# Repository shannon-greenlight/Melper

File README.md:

# The Melper
The Melper converts a Moog case into a powered Eurorack case.

It requires +12V as an input and generates -12V and +5V.
These 3 voltage rails supply 6 Eurorack power connectors.
Three LEDs monitor the supply rails.
It is targeted to Moog cases, but can be used in any case that has +12V.
The 12 volt wall wart that Moog supplies works well. 

This repo contains the schematic and layout files needed to create the Melper.
These files are for KiCAD Version: 8.0.8

The repo contains the BOM files that are used to buy the components.
These are found in the _BOM_ folder.
The BOM files for DigiKey and JLCPCB are provided in .csv format.
Other suppliers typically will accept these files with minor modifications.

The repo also contains the files needed for fabrication. These are found in the _fab_ folder.
These include the gerber files, which are provided both as a zip file and as the full unzipped folder structure.
Also included in the _fab_ folder are the files needed for pick-and-place.
The .xlsx file is the pick-and-place file. It is formatted for JLCPCB.
The raw position files are found in the _pos_ folder.

# Specs
The Melper derives -12V and +5V from the +12V supply.
- -12V
	- Voltage range: -11.75V thru -12.25V
	- Maximum current: 200mA
	- Line regulation: 15mV
	- Load regulation: 20mV
	- Ripple: 230mV
- +5V (see - [LM7805](https://www.ti.com/lit/ds/symlink/lm7800.pdf))
	- Voltage range: +4.8V thru +5.2V
	- Maximum current: 500mA @ 25C (more if heat-sink is used)
	- Line regulation: 3mV typ.
	- Load regulation: 10mV typ.
	- Ripple rejection: 80dB typ.

# Making Changes
The process of making changes usually starts with altering the schematic followed by other actions as required.
This requires a properly configured KiCAD installation. Download the KiCAD [repo](https://github.com/shannon-greenlight/KiCAD) and follow the instructions in the README to install.
When the system is configured follow the steps outlined below. Some steps are optional depending on what has changed.

These procedures have been optimized for use with Digi-Key and JLCPCB. They should be a good starting point for use with other vendors.

- Update schematic
- If any parts have changed, Update BOMs
	- From KiCAD Schematic Editor, run Tools->Generate Legacy Bill of Materials using bom2grouped_csv.xsl
		- bom2grouped_csv.xsl is found in the Greenface KiCAD repo.
		- Here is a sample command line: xsltproc -o "%O.csv" "C:\Users\shann\Dropbox\KiCAD\bom2grouped_csv.xsl" "%I"
		- This creates a .csv and an xsl file. The xml file is used in the next step.
	- Run _generate_boms.bat_
		- This creates 3 .csv files
			- BOM\Digi-Key\Melper_full.csv (all components)
			- BOM\Digi-Key\Melper_split.csv (just components not found in LCSC BOM)
			- BOM\LCSC\Melper_bom.csv (just components to be assembled by JLCPCB)
		- generate_boms.bat requires Python and the Greenface Python [libraries](https://github.com/shannon-greenlight/PYTHON_BOM) to be installed
			- Place the Greenface Python folder in a convienient place on your computer and set the variable %plugin_dir% to point to that folder location.
			- Python is invoked as 'py' in the batch file. This may need to be changed depending on your Python installation.
- Update layout if required
	- Plot the Gerber files
		- Set the output directory to _fab\gerber\\_
		- Make sure to Generate Drill Files
		- Create a zip archive of the Gerber files. (This is required by JLCPCB)
			- Use Windows Send To Compressed Folder. Rename the resulting file to melper_gerbers.zip
			- Alternatively, use zip_gerbers.bat
			- zip_gerbers.bat requires 7z.exe
			- Edit this file if 7z.exe is installed somewhere other than C:\Program Files\7-Zip
	- Create the pick-and-place files
		- From KiCAD PCB Editor, run File->Fabrication Outputs->Component Placement
		- Set the output directory to _fab\pos\\_
		- This creates the files used by the next step
		- Update melper_cpl.xlsx
			- melper_cpl.xlsx uses Excel Queries to convert pos\Melper-top-pos.csv into a format compatible with JLCPCB
			- Excel requires an absolute path to the source folder of the data. Edit the query to enter the path to your project.
			- *note: This process does not produce a perfect placement file due to differences in how KiCAD and JLCPCB orient components. However, JLCPCB is able to use the file without problems. So, even if the placement looks wrong when specifying the build, they will use the file and produce correct boards.
			- **note: There is probably a KiCAD plugin available that does a better job. The user is encouraged to try this route and report the results back.
- Upload to JLCPCB
	- JLCPCB requires the following files:
		- fab\melper_gerbers.zip
		- fab\melper_cpl.xlsx (only needed for assembly)
		- bom\LCSC\Melper_bom.csv (only needed for assembly)

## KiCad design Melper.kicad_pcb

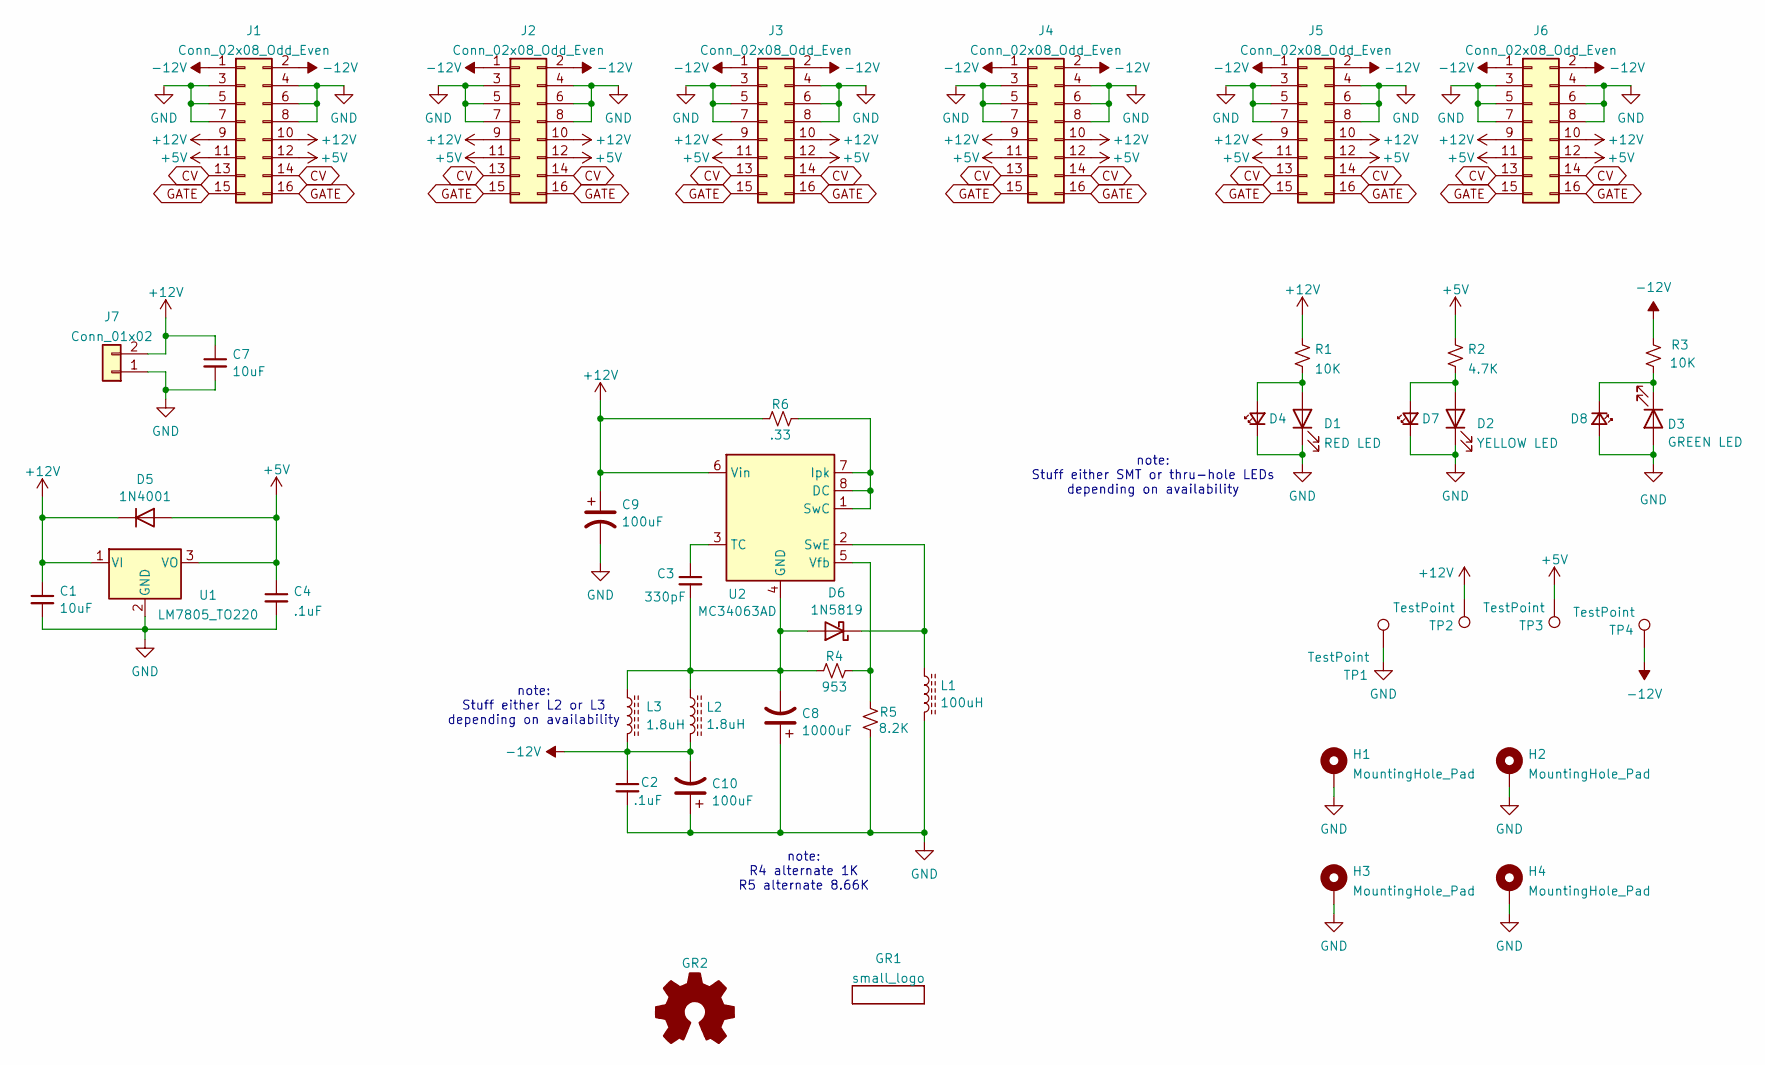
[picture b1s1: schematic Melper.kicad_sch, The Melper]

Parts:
C1, C7: 10uF; C_Disc_D5.1mm_W3.2mm_P5.00mm; Digi-Key Part 445-173437-1-ND
C2, C4: .1uF; C_Disc_D4.3mm_W1.9mm_P5.00mm; Digi-Key Part 399-9877-1-ND
C3: 330pF; C_Disc_D4.3mm_W1.9mm_P5.00mm; Digi-Key Part 399-4231-ND
C8: 1000uF; CP_Radial_D10.0mm_P5.00mm; Digi-Key Part 1189-1545-1-ND
C9, C10: 100uF; CP_Radial_D6.3mm_P2.50mm; Digi-Key Part 1189-1300-ND
D1: RED LED; LED_D3.0mm; Digi-Key Part 160-1035-ND
D2: YELLOW LED; LED_D3.0mm; Digi-Key Part 160-1961-ND
D3: GREEN LED; LED_D3.0mm; Digi-Key Part 732-5008-ND
D4: Red SMT LED; LED_0603_1608Metric_Pad1.05x0.95mm_HandSolder; LCSC Part # C2286
D5: 1N4001; D_DO-41_SOD81_P10.16mm_Horizontal; Digi-Key Part 1N4001RLGOSCT-ND
D6: 1N5819; D_DO-41_SOD81_P7.62mm_Horizontal; Digi-Key Part 497-6610-1-ND
D7: Yellow SMT LED; LED_0603_1608Metric_Pad1.05x0.95mm_HandSolder; LCSC Part # C72038
D8: Blue SMT LED; LED_0603_1608Metric_Pad1.05x0.95mm_HandSolder; LCSC Part # C2288
GR1: small_logo; small_face
GR2: Logo_Open_Hardware_Small; OSHW-Logo_5.7x6mm_SilkScreen
H1, H2, H3, H4: MountingHole_Pad; MountingHole_3.2mm_M3_DIN965_Pad
J1, J2, J3, J4, J5, J6: Conn_02x08_Odd_Even; PinHeader_2x08_P2.54mm_Vertical; Digi-Key Part S9171-ND
J7: Conn_01x02; PinHeader_1x02_P2.54mm_Vertical; Digi-Key Part 900-0022232021-ND
L1: 100uH; L_Radial_D8.7mm_P5.00mm_Fastron_07HCP; Digi-Key Part RLB0914-101KL-ND
L2: 1.8uH; L_Axial_L9.5mm_D4.0mm_P12.70mm_Horizontal_Fastron_SMCC; Digi-Key Part 495-76032-1-ND
L3: 1.8uH; L_Sunlord_SWPA4012S; LCSC Part # C96867
R1, R3: 10K; R_Axial_DIN0207_L6.3mm_D2.5mm_P10.16mm_Horizontal; Digi-Key Part S10KQCT-ND
R2: 4.7K; R_Axial_DIN0207_L6.3mm_D2.5mm_P10.16mm_Horizontal; Digi-Key Part CF14JT4K70CT-ND
R4: 953; R_Axial_DIN0207_L6.3mm_D2.5mm_P10.16mm_Horizontal; Digi-Key Part 13-MFR-25FRF52-953RCT-ND
R5: 8.2K; R_Axial_DIN0207_L6.3mm_D2.5mm_P10.16mm_Horizontal; Digi-Key Part MFR-25FBF52-8K2-ND
R6: .33; R_Axial_DIN0207_L6.3mm_D2.5mm_P10.16mm_Horizontal; Digi-Key Part A138238CT-ND
TP1: TestPoint; TestPoint_Keystone_5005-5009_Compact; Digi-Key Part 36-5006-ND
TP2, TP3, TP4: TestPoint; TestPoint_Pad_D2.0mm
U1: LM7805_TO220; TO-220-3_Horizontal_TabDown; Digi-Key Part 497-12404-ND
U2: MC34063AD; DIP-8_W7.62mm_LongPads; Digi-Key Part 497-7412-5-ND

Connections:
+5V: C4.1, D5.2 (A), J1.11, J1.12, J2.11, J2.12, J3.11, J3.12, J4.11, J4.12, J5.11, J5.12, J6.11, J6.12, R2.1, TP3.1, U1.3 (VO)
+12V: C1.1, C7.1, C9.1, D5.1 (K), J1.9, J1.10, J2.9, J2.10, J3.9, J3.10, J4.9, J4.10, J5.9, J5.10, J6.9, J6.10, J7.2, R1.1, R6.1, TP2.1, U1.1 (VI), U2.6 (Vin)
-12V: C2.1, C10.2, J1.1, J1.2, J2.1, J2.2, J3.1, J3.2, J4.1, J4.2, J5.1, J5.2, J6.1, J6.2, L2.2, L3.2, R3.2, TP4.1
CV: J1.13, J1.14, J2.13, J2.14, J3.13, J3.14, J4.13, J4.14, J5.13, J5.14, J6.13, J6.14
GATE: J1.15, J1.16, J2.15, J2.16, J3.15, J3.16, J4.15, J4.16, J5.15, J5.16, J6.15, J6.16
GND: C1.2, C2.2, C4.2, C7.2, C8.1, C9.2, C10.1, D1.1 (K), D2.1 (K), D3.2 (A), D4.1 (K), D7.1 (K), D8.2 (A), H1.1, H2.1, H3.1, H4.1, J1.3, J1.4, J1.5, J1.6, J1.7, J1.8, J2.3, J2.4, J2.5, J2.6, J2.7, J2.8, J3.3, J3.4, J3.5, J3.6, J3.7, J3.8, J4.3, J4.4, J4.5, J4.6, J4.7, J4.8, J5.3, J5.4, J5.5, J5.6, J5.7, J5.8, J6.3, J6.4, J6.5, J6.6, J6.7, J6.8, J7.1, L1.2, R5.1, TP1.1, U1.2 (GND)
unnamed: D1.2 (A), D4.2 (A), R1.2
unnamed: D2.2 (A), D7.2 (A), R2.2
unnamed: D3.1 (K), D8.1 (K), R3.1
unnamed: C3.2, C8.2, D6.2 (A), L2.1, L3.1, R4.1, U2.4 (GND)
unnamed: D6.1 (K), L1.1, U2.2 (SwE)
unnamed: R6.2, U2.1 (SwC), U2.7 (Ipk), U2.8 (DC)
unnamed: C3.1, U2.3 (TC)
unnamed: R4.2, R5.2, U2.5 (Vfb)

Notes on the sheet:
note: Stuff either L2 or L3 depending on availability
note: R4 alternate 1K R5 alternate 8.66K
note: Stuff either SMT or thru-hole LEDs depending on availability

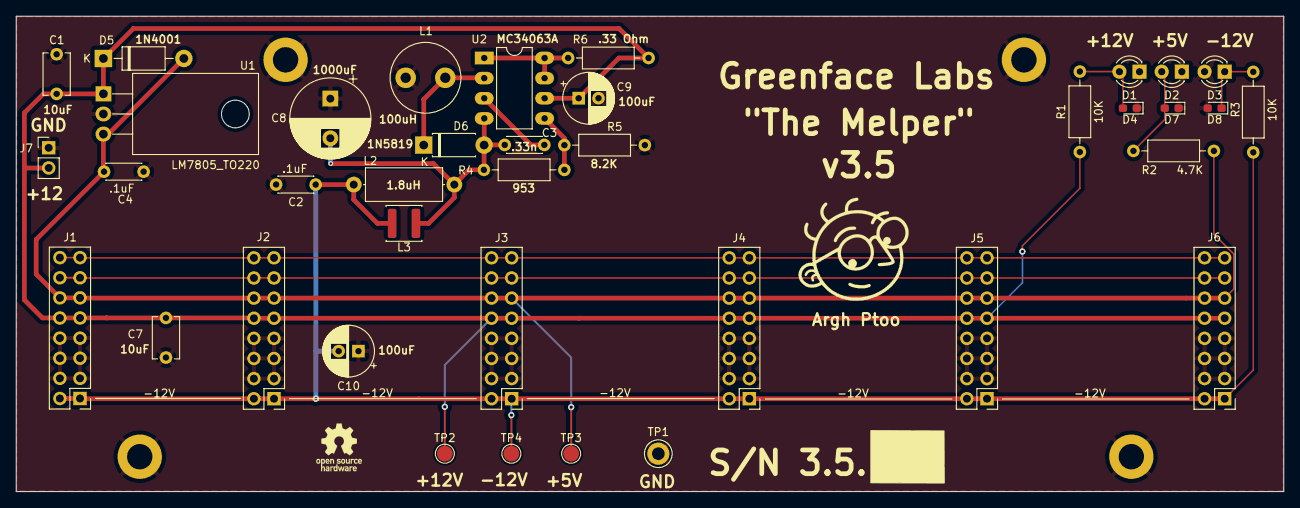
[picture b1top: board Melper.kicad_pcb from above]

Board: 2 copper layers, 160.0 x 60.0 mm, 44 parts (0 on the bottom side), 14 nets.

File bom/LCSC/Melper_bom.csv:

"Designator","Comment","Footprint","JLCPCBPart#"
"C1, C7, ","10uF","Capacitor_THT:C_Disc_D5.1mm_W3.2mm_P5.00mm","C531341 "
"C2, C4, ",".1uF","Capacitor_THT:C_Disc_D4.3mm_W1.9mm_P5.00mm","C84772 "
"C3, ","330pF","Capacitor_THT:C_Disc_D4.3mm_W1.9mm_P5.00mm","C2896045"
"C8, ","1000uF","Capacitor_THT:CP_Radial_D10.0mm_P5.00mm","C43909"
"C9, C10, ","100uF","Capacitor_THT:CP_Radial_D6.3mm_P2.50mm","C45075"
"D4, ","Red SMT LED","LED_SMD:LED_0603_1608Metric_Pad1.05x0.95mm_HandSolder","C2286"
"D5, ","1N4001","Diode_THT:D_DO-41_SOD81_P10.16mm_Horizontal","C895212"
"D6, ","1N5819","Diode_THT:D_DO-41_SOD81_P7.62mm_Horizontal","C110032"
"D7, ","Yellow SMT LED","LED_SMD:LED_0603_1608Metric_Pad1.05x0.95mm_HandSolder","C72038"
"D8, ","Blue SMT LED","LED_SMD:LED_0603_1608Metric_Pad1.05x0.95mm_HandSolder","C2288"
"J1, J2, J3, J4, J5, J6, ","Conn_02x08_Odd_Even","Connector_PinHeader_2.54mm:PinHeader_2x08_P2.54mm_Vertical","C305956"
"J7, ","Conn_01x02","Connector_PinHeader_2.54mm:PinHeader_1x02_P2.54mm_Vertical","C2905434"
"L1, ","100uH","Inductor_THT:L_Radial_D8.7mm_P5.00mm_Fastron_07HCP","C7343084"
"L2, ","1.8uH","Inductor_THT:L_Axial_L9.5mm_D4.0mm_P12.70mm_Horizontal_Fastron_SMCC","C17370623"
"L3, ","1.8uH","Inductor_SMD:L_Sunlord_SWPA4012S","C96867"
"R1, R3, ","10K","Resistor_THT:R_Axial_DIN0207_L6.3mm_D2.5mm_P10.16mm_Horizontal","C57436 "
"R2, ","4.7K","Resistor_THT:R_Axial_DIN0207_L6.3mm_D2.5mm_P10.16mm_Horizontal","C176521"
"R4, ","953","Resistor_THT:R_Axial_DIN0207_L6.3mm_D2.5mm_P10.16mm_Horizontal","C57435"
"R5, ","8.2K","Resistor_THT:R_Axial_DIN0207_L6.3mm_D2.5mm_P10.16mm_Horizontal","C172593"
"R6, ",".33","Resistor_THT:R_Axial_DIN0207_L6.3mm_D2.5mm_P10.16mm_Horizontal","C119970"
"TP1, ","TestPoint","TestPoint:TestPoint_Keystone_5005-5009_Compact","C238124 "
"U1, ","LM7805_TO220","Package_TO_SOT_THT:TO-220-3_Horizontal_TabDown","C111887 "
"U2, ","MC34063AD","Package_DIP:DIP-8_W7.62mm_LongPads","C5180"

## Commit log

2022-12-15 Init checkin of project
2022-12-15 Update Melper.kicad_sch
    Changes LED resistors.
2022-12-15 Adds BOM
2022-12-17 Work on images.
2023-10-19 Version 2.1
2023-10-20 Version 3
    Adds 6th power connector.
2024-05-06 Rev 3.2
2025-07-07 Revision 3.5
    Changes negative regulator.
    Adds support for JLC build.
2025-07-08 Removes image files
    Removes unneeded image files from repo.
2025-07-11 Update README.md
    Adds voltage range spec
